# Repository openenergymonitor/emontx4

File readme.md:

# EmonTx v4

The emonTx v4 is an energy monitoring transmitter unit that can monitor up to 6 AC circuits using CT sensors and the OpenEnergyMonitor 1-3 phase voltage sensing unit. At it's core is a Microchip AVR128DB48 microcontroller - responsible for sampling the current and voltage waveforms and calculating the power and energy values. The emonTx v4 also supports temperature sensing and pulse counting.

Data from the emonTx can be transmitted over the 433 MHz RFM69cw radio link or read directly using a USB cable from an emonBase or emonPi. A number of adapter boards are also available to provide internal connectivity options via ESP32, ESP8266, Pi Pico W and Pi Zero W.

**Key features**

* Micro-controller: AVR128DB48 (VQFN 128 kb flash, 48-pin package)
* 3 voltage channels (via RJ11 connector top-right, interfaces with separate voltage sensing board, single phase firmware only at present).
* 6 CT current channels on the base board.
* Option to extend the number of CT channels to 12 via an additional extender board (firmware not yet developed for this).
* Precision voltage reference for the ADC to improve accuracy.
* RJ45 socket for pulse counter and DS18B20 temperature sensing.
* 3x 3-WAY pluggable terminal blocks for selectable temperature sensing, pulse or additional analog input.
* RFM69CW 433MHz radio transceiver
* DIP Switch to select node id
* USB-C power and integrated CP2102 usb to serial chip
* Serial and SPI pin headers breakout internally, designed for use with adapter boards.
 
The dimensions are slightly smaller than that of the emonTx v3 at 65mm long rather than 80mm.

The board is designed to support both single and full 3-phase electricity monitoring when used in conjunction with the relevant external voltage sensing board. And the CT extender pin headers should provide a cost effective way of gaining additional CT channels.

The on-board USB to serial chip will make it easier and neater to have a hard-wired installation linking the emonTx to a RaspberryPi based base station.

## Documentation

[View on read the docs](https://docs.openenergymonitor.org/emontx4/index.html)

Or here on github:

- [Install Guide](docs/emontx4_emonbase_install.md)
- [Configuration](docs/configuration.md)
- [Firmware](docs/firmware.md)
- [Expansion boards](docs/expansion_boards.md)

## Expansion Boards

- [6CT Expansion Board](https://github.com/openenergymonitor/emontx4/tree/main/expansion_boards/CTExt)
- [ESP8266 Expansion Board](https://github.com/openenergymonitor/emontx4/tree/main/expansion_boards/ESP8266)
- [ESP32 Expansion Board](https://github.com/openenergymonitor/emontx4/tree/main/expansion_boards/ESP32)
- [Pi Pico Expansion Board](https://github.com/openenergymonitor/emontx4/tree/main/expansion_boards/PiPico)
- [Pi Zero ExtExpansionension Board](https://github.com/openenergymonitor/emontx4/tree/main/expansion_boards/PiZero)

## Community & Support

- [OpenEnergyMonitor Forums](https://community.openenergymonitor.org)

OpenEnergyMonitor Shop Support: support@openenergymonitor.zendesk.com

## License

- The hardware designs (schematics and CAD files) are licensed under a Creative Commons Attribution-ShareAlike 3.0 Unported License.
- The firmware is released under the GNU GPL V3 license The documentation is subject to GNU Free Documentation License
- The hardware designs follow the terms of the OSHW (Open-source hardware) Statement of Principles 1.0.

## Disclaimer

```
OUR PRODUCTS AND ASSEMBLY KITS MAY BE USED BY EXPERIENCED, SKILLED USERS, AT THEIR OWN RISK. TO THE FULLEST EXTENT PERMISSIBLE BY THE APPLICABLE LAW, WE HEREBY DISCLAIM ANY AND ALL RESPONSIBILITY, RISK, LIABILITY AND DAMAGES ARISING OUT OF DEATH OR PERSONAL INJURY RESULTING FROM ASSEMBLY OR OPERATION OF OUR PRODUCTS.

Your safety is your own responsibility, including proper use of equipment and safety gear, and determining whether you have adequate skill and experience. OpenEnergyMonitor and Megni registered partnership disclaims all responsibility for any resulting damage, injury, or expense. It is your responsibility to make sure that your activities comply with applicable laws, including copyright. Always check the webpage associated with each unit before you get started. There may be important updates or corrections. All use of the instructions, kits, projects and suggestions given both by megni.co.uk, openenergymonitor.org and shop.openenergymonitor.org are to be used at your own risk. The technology (hardware , firmware and software) are constantly changing, documentation (including build guide and instructions) may not be complete or correct.

If you feel uncomfortable with assembling or using any part of the system, return it to us for a full refund.
```

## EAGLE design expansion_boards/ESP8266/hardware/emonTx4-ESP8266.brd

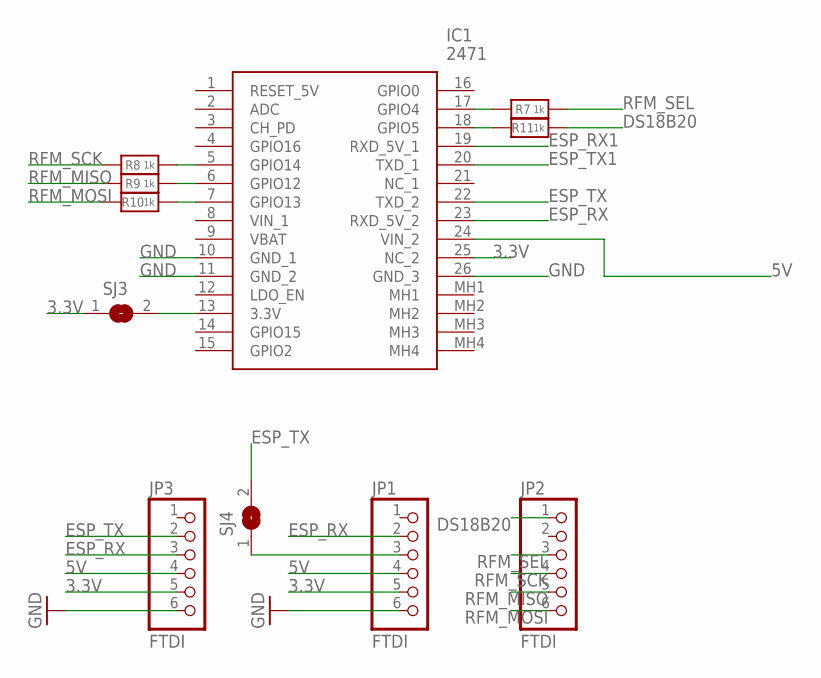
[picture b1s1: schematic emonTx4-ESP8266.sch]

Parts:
IC1: 2471
JP1, JP2, JP3: FTDI; 1X06_ROUND_70
R7, R8, R9, R10, R11: 1k; _0603
SJ3, SJ4: SJ

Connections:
3.3V: IC1.25 (NC_2), JP1.5, JP3.5, SJ3.1
5V: IC1.24 (VIN_2), JP1.4, JP3.4
DS18B20: JP2.1, R11.1
ESP_RX: IC1.23 (RXD_5V_2), JP1.2, JP3.3
ESP_RX1: IC1.19 (RXD_5V_1)
ESP_TX: IC1.22 (TXD_2), JP3.2, SJ4.2
ESP_TX1: IC1.20 (TXD_1)
GND: IC1.10 (GND_1), IC1.11 (GND_2), IC1.26 (GND_3), JP1.6, JP3.6
unnamed: JP1.3, SJ4.1
unnamed: IC1.13 (3.3V), SJ3.2
unnamed: IC1.17 (GPIO4), R7.2
unnamed: IC1.5 (GPIO14), R8.1
unnamed: IC1.6 (GPIO12), R9.1
unnamed: IC1.7 (GPIO13), R10.1
unnamed: IC1.18 (GPIO5), R11.2
RFM_MISO: JP2.5, R9.2
RFM_MOSI: JP2.6, R10.2
RFM_SCK: JP2.4, R8.2
RFM_SEL: JP2.3, R7.1

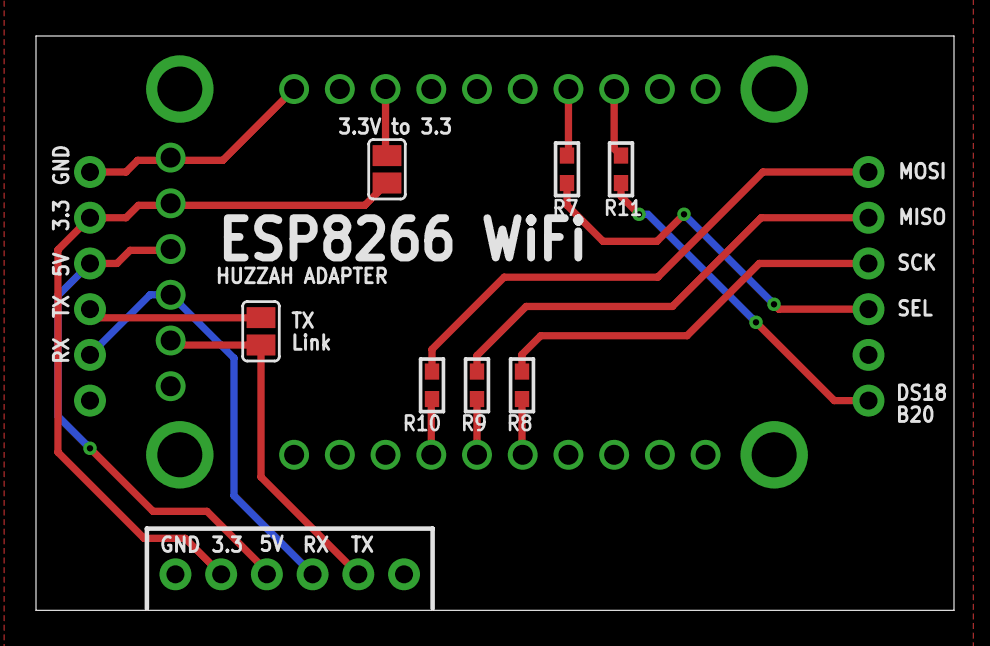
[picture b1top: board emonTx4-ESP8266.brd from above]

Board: 2 copper layers, 51.0 x 31.9 mm, 11 parts (1 on the bottom side), 17 nets.

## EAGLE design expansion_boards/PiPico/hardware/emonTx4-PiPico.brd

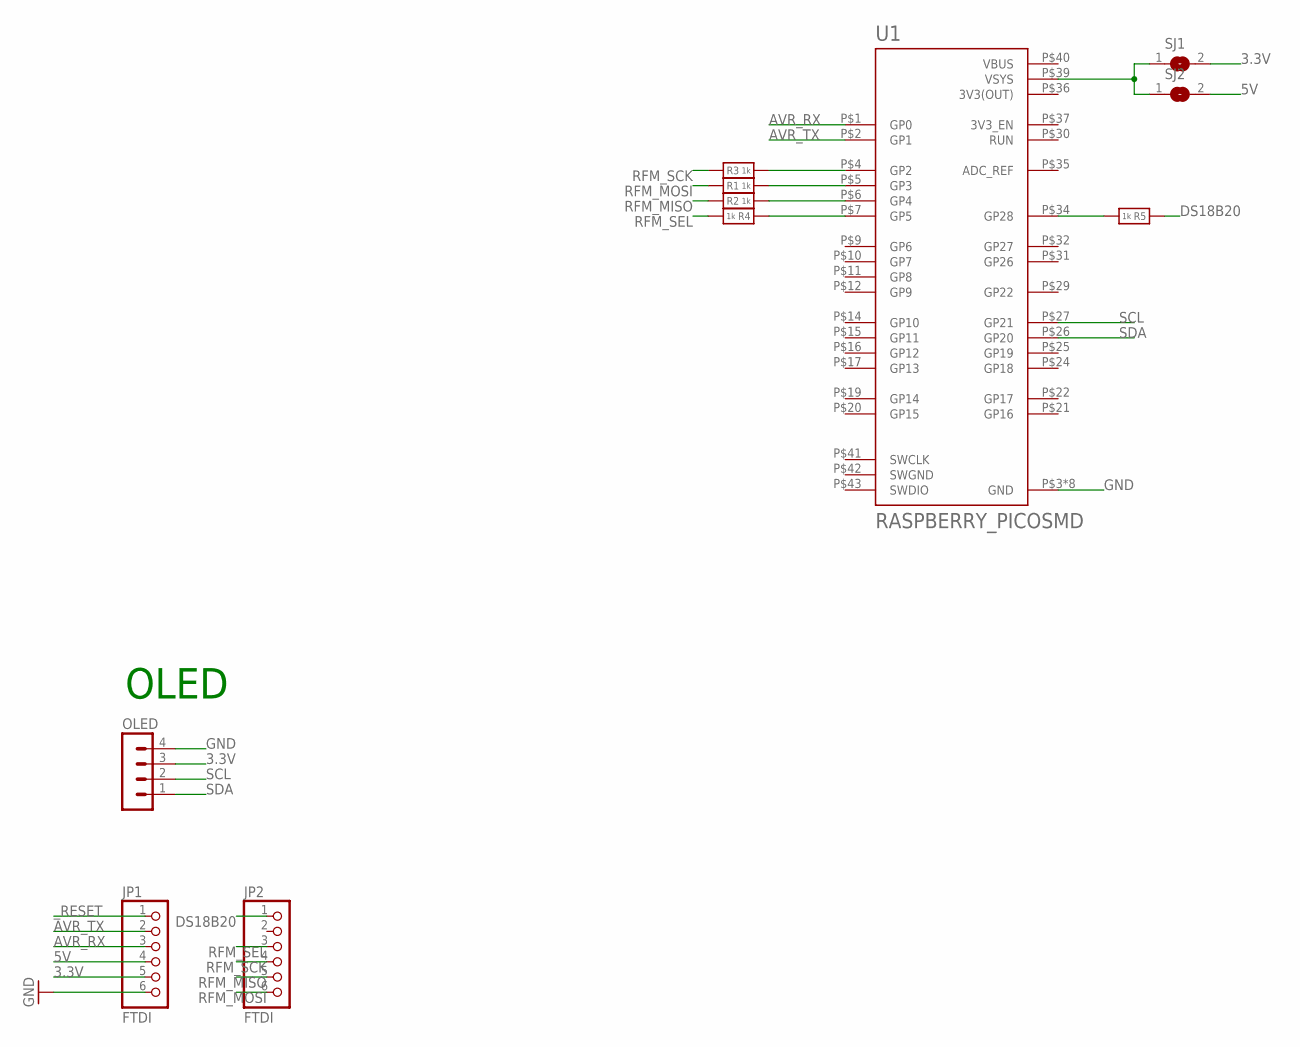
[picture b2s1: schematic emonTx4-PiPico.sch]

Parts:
JP1, JP2: FTDI; 1X06_ROUND_70
OLED: MA04-1-OLEDOLED; MA04-1-OLED
R1, R2, R3, R4, R5: 1k; _0603
SJ1, SJ2: SJ
U1: RASPBERRY_PICOSMD; PICO-PKG-SMD

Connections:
3.3V: JP1.5, OLED.3, SJ1.2
3V3(OUT): U1.P$36 (3V3(OUT))
5V: JP1.4, SJ2.2
AVR_RX: JP1.3, U1.P$1 (GP0)
AVR_TX: JP1.2, U1.P$2 (GP1)
DS18B20: JP2.1, R5.2
GND: JP1.6, OLED.4, U1.P$3 (GND), U1.P$8 (GND), U1.P$13 (GND), U1.P$18 (GND), U1.P$23 (GND), U1.P$28 (GND), U1.P$33 (GND), U1.P$38 (GND)
unnamed: SJ1.1, SJ2.1, U1.P$39 (VSYS)
unnamed: R3.1, U1.P$4 (GP2)
unnamed: R1.1, U1.P$5 (GP3)
unnamed: R2.1, U1.P$6 (GP4)
unnamed: R4.2, U1.P$7 (GP5)
unnamed: R5.1, U1.P$34 (GP28)
RFM_MISO: JP2.5, R2.2
RFM_MOSI: JP2.6, R1.2
RFM_SCK: JP2.4, R3.2
RFM_SEL: JP2.3, R4.1
SCL: OLED.2, U1.P$27 (GP21)
SDA: OLED.1, U1.P$26 (GP20)
SWGND: U1.P$42 (SWGND)
VBUS: U1.P$40 (VBUS)
_RESET: JP1.1

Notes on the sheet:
OLED

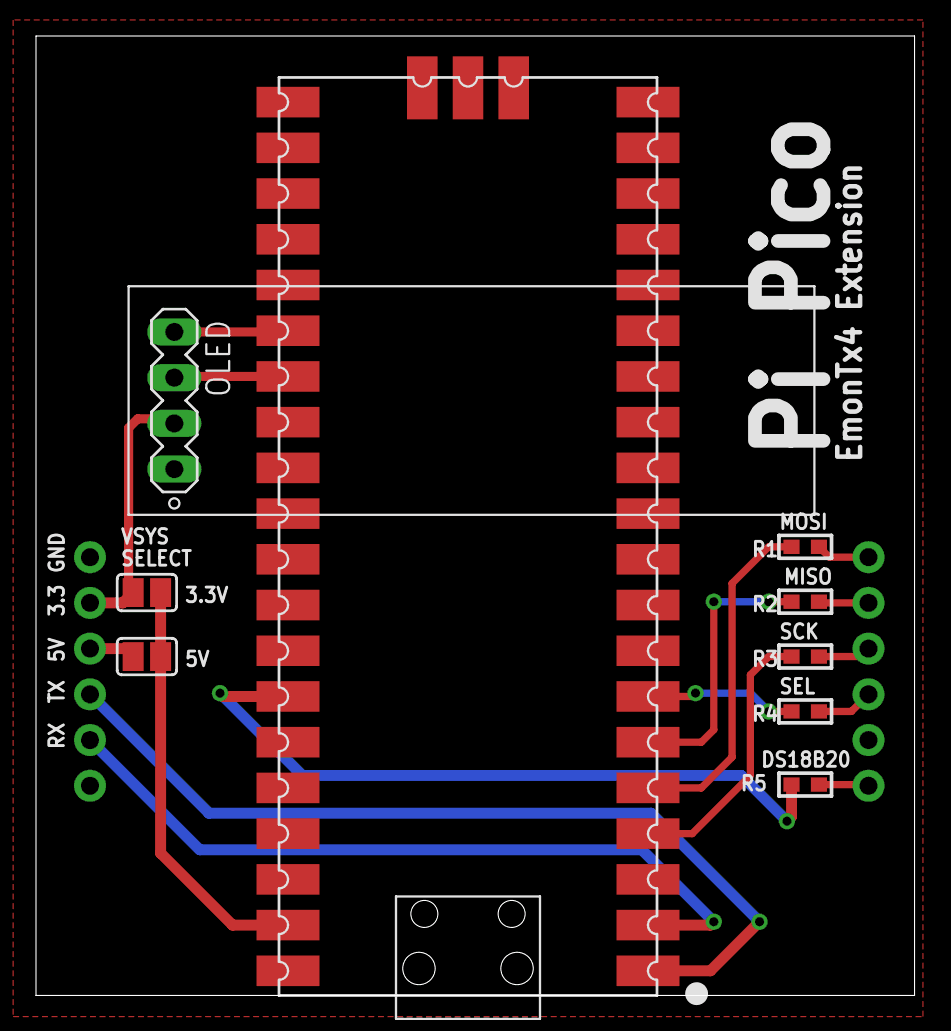
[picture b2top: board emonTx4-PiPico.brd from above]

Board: 2 copper layers, 48.8 x 53.3 mm, 11 parts (0 on the bottom side), 18 nets.

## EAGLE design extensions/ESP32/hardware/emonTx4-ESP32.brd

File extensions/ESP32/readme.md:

# EmonTx v4 ESP32 Extension Board

### Software examples:

- [Basic emoncms client](https://github.com/openenergymonitor/emontx4/tree/main/extensions/ESP32/examples/basic_emoncms_client)
- [RFM69cw test](https://github.com/openenergymonitor/emontx4/tree/main/extensions/ESP32/examples/rfm69cw_test)

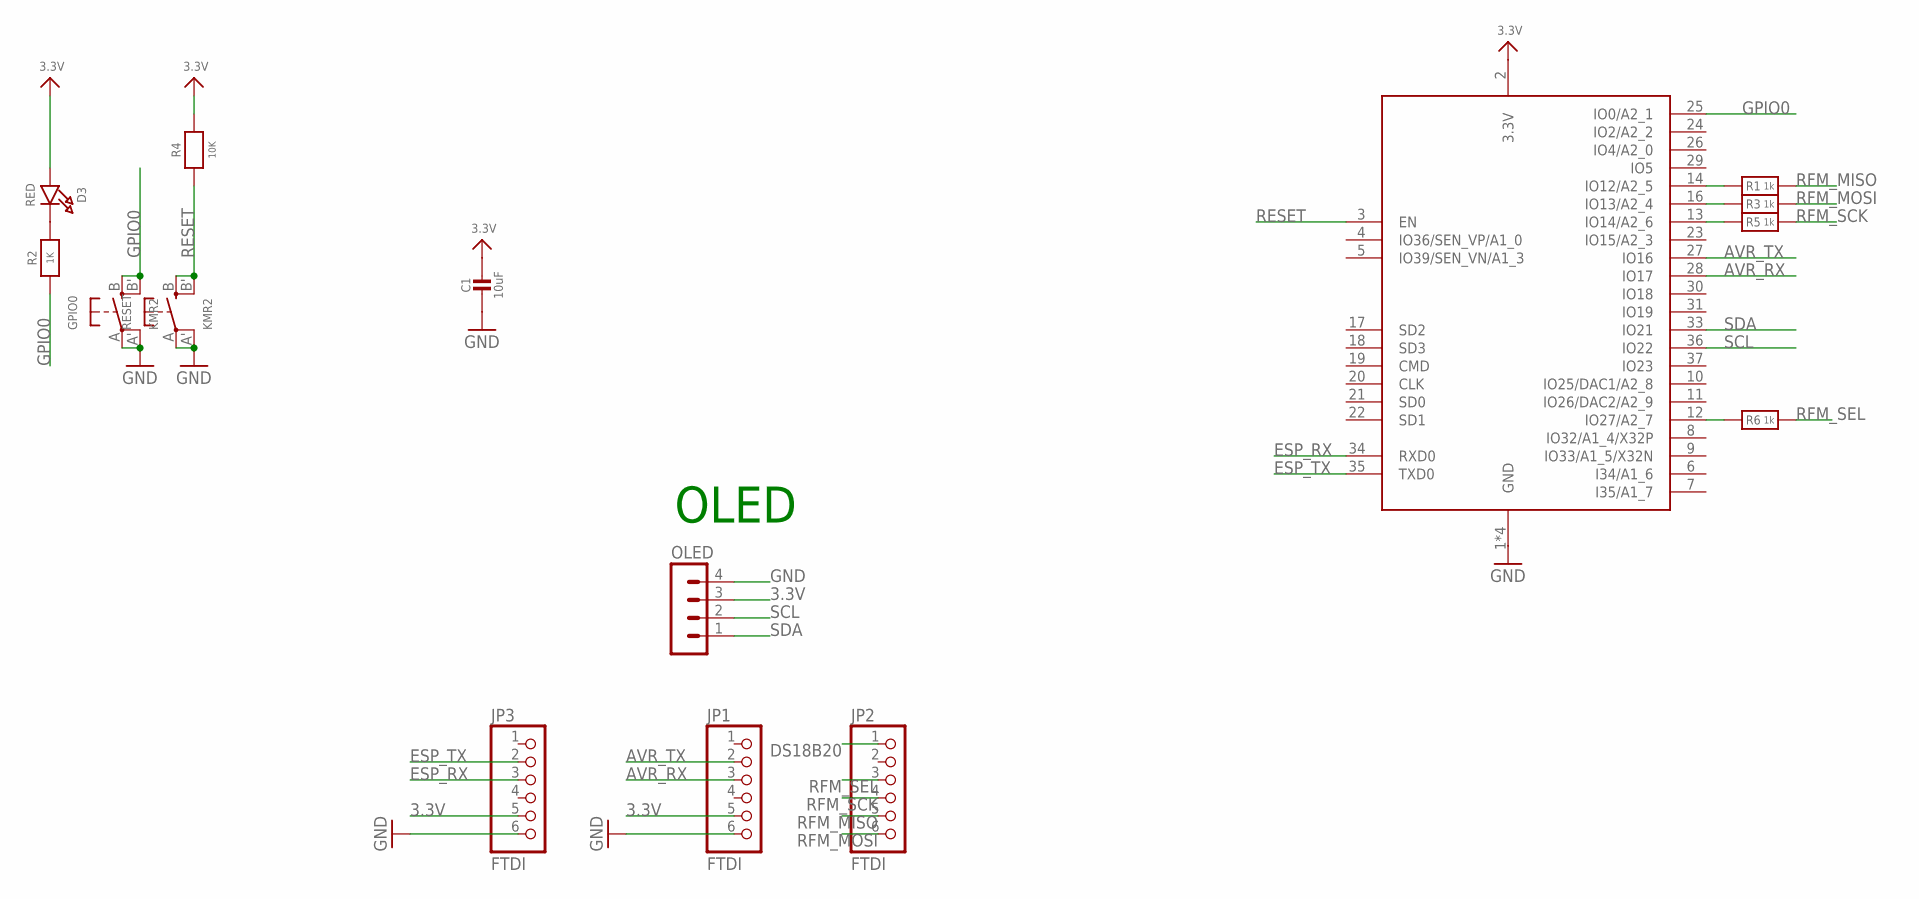
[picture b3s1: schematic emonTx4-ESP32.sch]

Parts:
C1: 10uF; _0603
D3: RED; CHIPLED_0603
GPIO0: KMR2; BTN_KMR2_4.6X2.8
JP1, JP2, JP3: FTDI; 1X06_ROUND_70
OLED: MA04-1-OLEDOLED; MA04-1-OLED
R1, R3, R5, R6: 1k; _0603
R2: 1K; _0603
R4: 10K; _0603
RESET: KMR2; BTN_KMR2_4.6X2.8
X2: ESP32_WROOM32; WROOM32

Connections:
3.3V: C1.1, D3.A, JP1.5, JP3.5, OLED.3, R4.2, X2.2 (3.3V)
AVR_RX: JP1.3, X2.28 (IO17)
AVR_TX: JP1.2, X2.27 (IO16)
DS18B20: JP2.1
ESP_RX: JP3.3, X2.34 (RXD0)
ESP_TX: JP3.2, X2.35 (TXD0)
GND: C1.2, GPIO0.A, GPIO0.A' (P1), JP1.6, JP3.6, OLED.4, RESET.A, RESET.A' (P1), X2.1 (GND), X2.15 (GND), X2.38 (GND), X2.P$1 (GND)
GPIO0: GPIO0.B (S), GPIO0.B' (S1), R2.1, X2.25 (IO0/A2_1)
unnamed: D3.C, R2.2
unnamed: R1.2, X2.14 (IO12/A2_5)
unnamed: R3.2, X2.16 (IO13/A2_4)
unnamed: R5.2, X2.13 (IO14/A2_6)
unnamed: R6.2, X2.12 (IO27/A2_7)
RESET: R4.1, RESET.B (S), RESET.B' (S1), X2.3 (EN)
RFM_MISO: JP2.5, R1.1
RFM_MOSI: JP2.6, R3.1
RFM_SCK: JP2.4, R5.1
RFM_SEL: JP2.3, R6.1
SCL: OLED.2, X2.36 (IO22)
SDA: OLED.1, X2.33 (IO21)

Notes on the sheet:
OLED

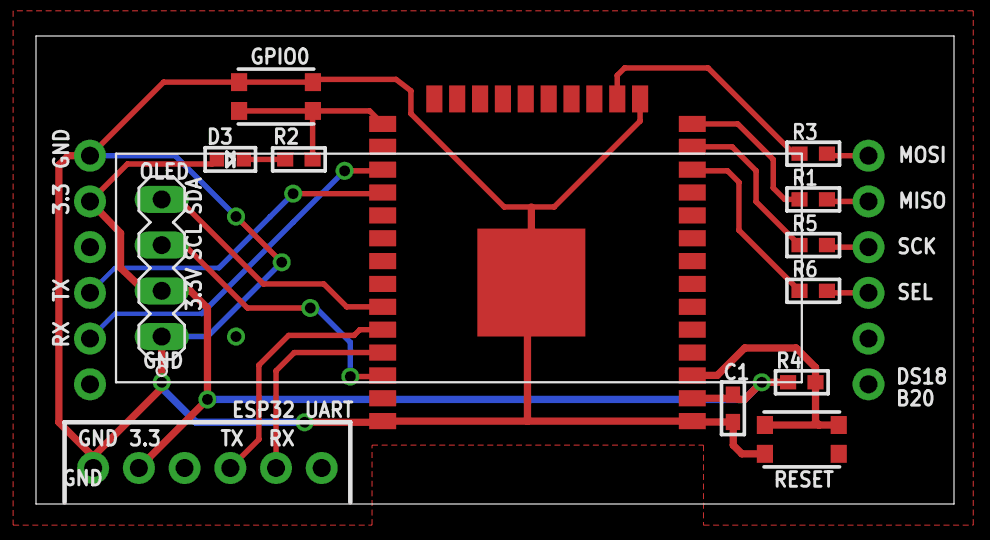
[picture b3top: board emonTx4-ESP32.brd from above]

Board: 2 copper layers, 51.0 x 26.0 mm, 15 parts (0 on the bottom side), 19 nets.

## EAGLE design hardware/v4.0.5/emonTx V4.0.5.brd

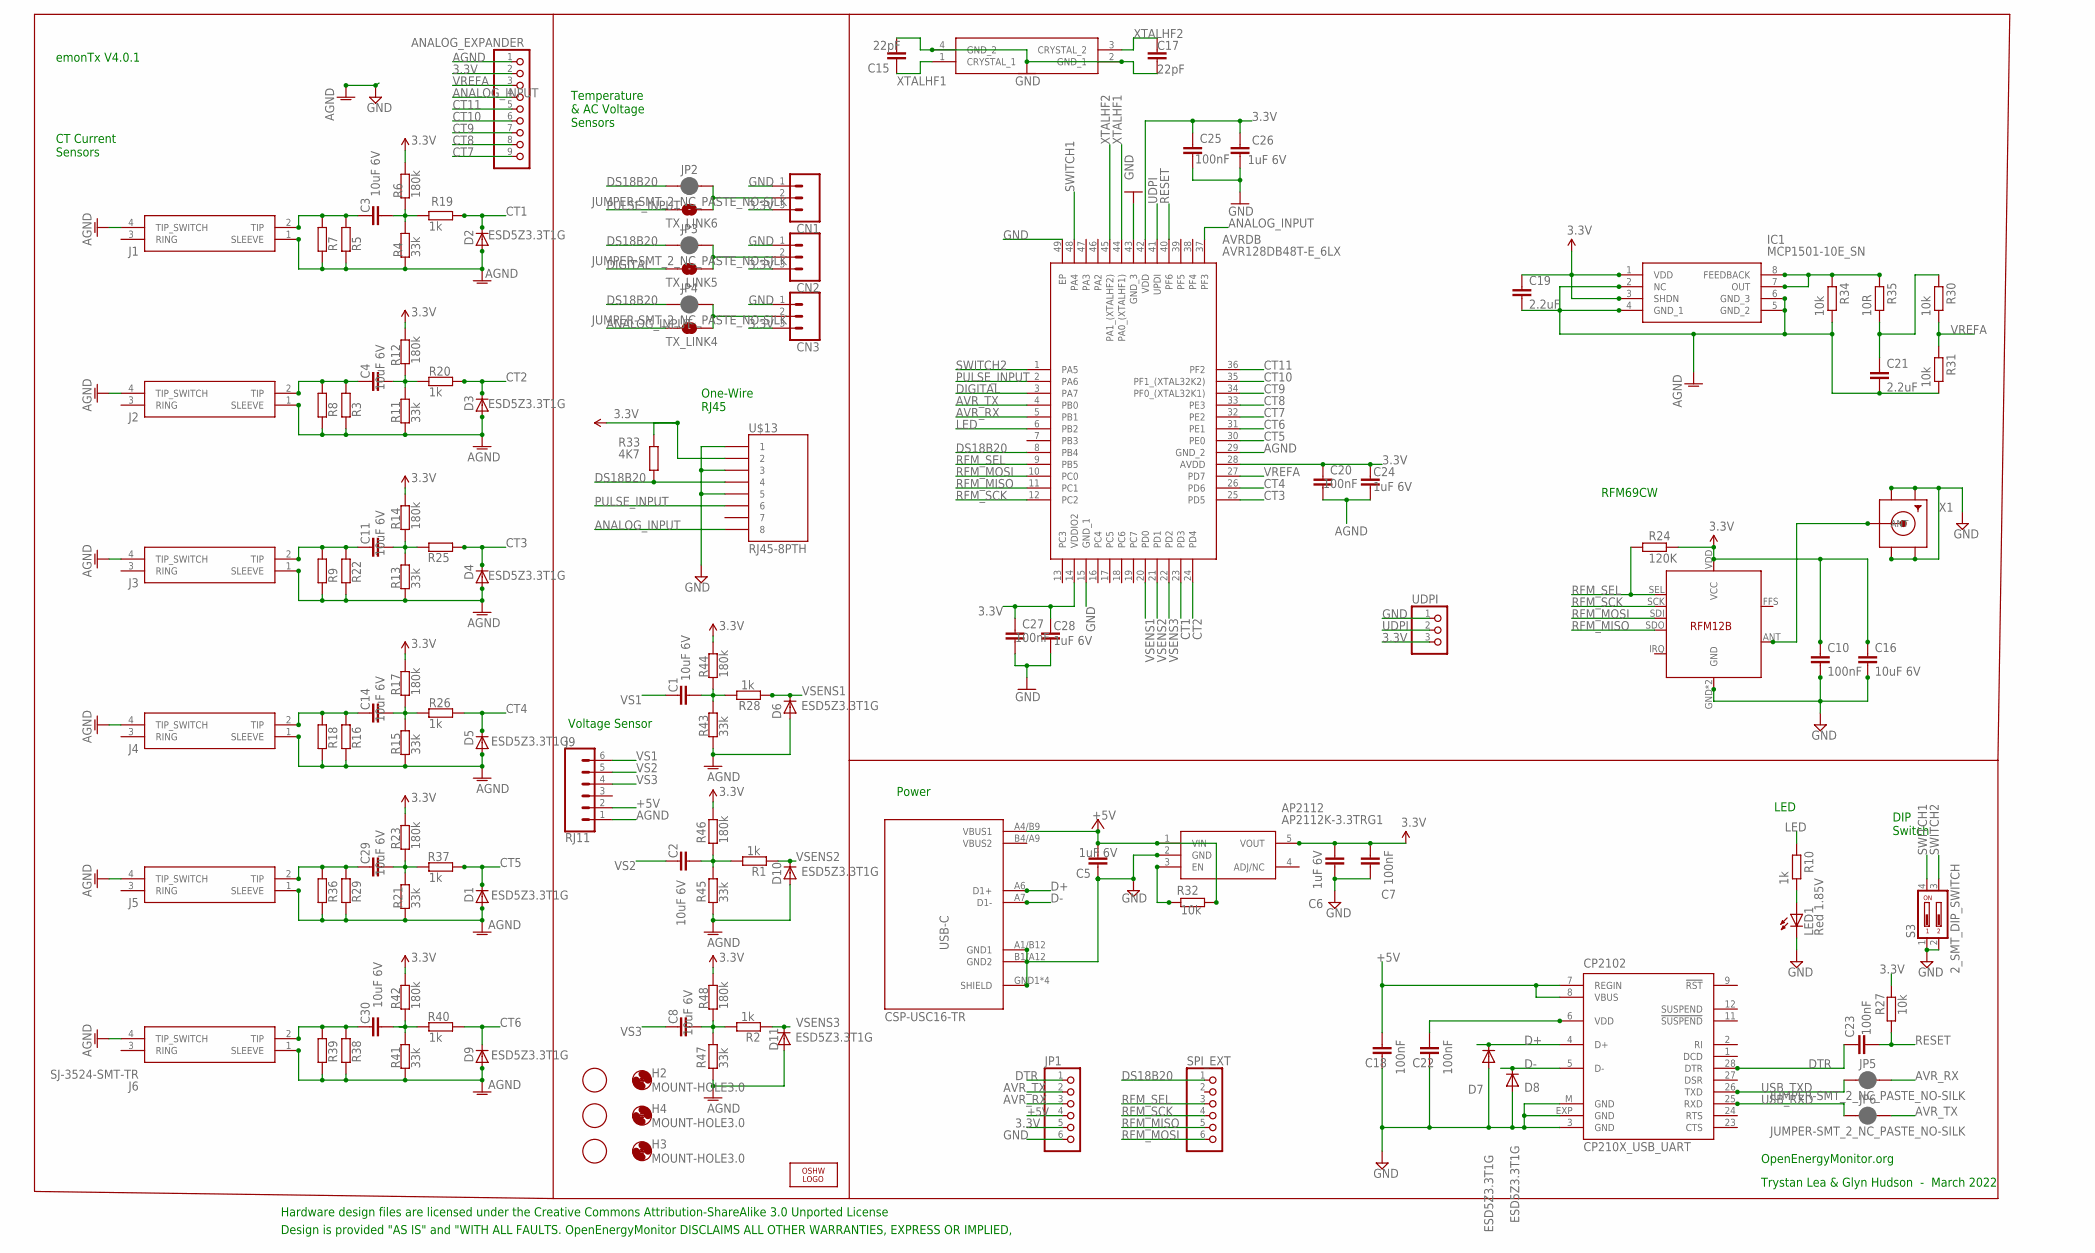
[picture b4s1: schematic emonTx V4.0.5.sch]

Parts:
ANALOG_EXPANDER: PINHD-1X9; 1X09-BIG
AP2112: AP2112K-3.3TRG1; SOT95P282X130-5N
AVRDB: AVR128DB48T-E_6LX; QFN40P600X600X90-49N
C1, C2, C3, C4, C8, C11, C14, C16, C29, C30: 10uF 6V; C0603
C5, C6, C24, C26, C28: 1uF 6V; C0603
C7, C10, C18, C20, C22, C23, C25, C27: 100nF; C0603
C15, C17: 22pF; C0603
C19, C21: 2.2uF; C0603
CN1, CN2, CN3: CONN_03SCREW; SCREWTERMINAL-3.5MM-3
CP2102: CP210X_USB_UART; MLP28
D1, D2, D3, D4, D5, D6, D7, D8, D9, D10, D11: ESD5Z3.3T1G; SOD-523
H2, H3, H4: MOUNT-HOLE3.0; 3,0
IC1: MCP1501-10E_SN; SOIC127P600X175-8N
J1, J2, J3, J4, J5, J6: SJ-3524-SMT-TR
J9: RJ11; RJ11-6
JP1: PINHD-1X6; 1X06
JP2, JP3, JP4, JP5, JP6: JUMPER-SMT_2_NC_PASTE_NO-SILK; SMT-JUMPER_2_NC_PASTE_NO-SILK
LED1: Red 1.85V; CHIP-LED0805
LOGO1: OSHW_LOGO_6MILX0200-NT; OSHW_6X200_NOTEXT
R1, R2, R10, R19, R20, R25, R26, R28, R37, R40: 1k; R0603
R3, R5, R16, R22, R29, R38: R-EU_0204/7; 0204/7
R4, R11, R13, R15, R21, R41, R43, R45, R47: 33k; R0603
R6, R12, R14, R17, R23, R42, R44, R46, R48: 180k; R0603
R7, R8, R9, R18, R36, R39: R-EU_R1206; R1206
R24: 120K; R0603
R27, R30, R31, R32, R34: 10k; R0603
R33: 4K7; R0603
R35: 10R; R0603
S3: 2_SMT_DIP_SWITCH; DIP_SWITCH_SMT
SPI_EXT: PINHD-1X6; 1X06
TX_LINK4, TX_LINK5, TX_LINK6: SOLDERJUMPERNC; SJ_2S
U$4, U$5, U$7: FIDUCIAL; FIDUCIAL_1MM
U$13: RJ45-8PTH; RJ45-8
U$14: RFM12B
UDPI: PINHD-1X3; 1X03
USB-C: CSP-USC16-TR; USB-C
X1: SMACONNECTOR; SMA90_DIP
XTAL: MCSJK-7U-12.00-12-10-80-B-10; MCSJK7U1200121080B10

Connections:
3.3V: ANALOG_EXPANDER.2, AP2112.5 (VOUT), AVRDB.14 (VDDIO2), AVRDB.28 (AVDD), AVRDB.42 (VDD), C6.2, C7.2, C10.1, C16.1, C19.1, C20.1, C24.1, C25.1, C26.1, C27.1, C28.1, CN1.3, CN2.3, CN3.3, IC1.1 (VDD), IC1.3 (SHDN), JP1.5, R6.2, R12.2, R14.2, R17.2, R23.2, R24.2, R27.2, R33.1, R42.2, R44.2, R46.2, R48.2, U$13.2, U$14.VDD (VCC), UDPI.3
+5V: AP2112.1 (VIN), C5.2, C18.2, CP2102.7 (REGIN), CP2102.8 (VBUS), J9.2, JP1.4, R32.1, USB-C.A4/B9 (VBUS1)
AGND: ANALOG_EXPANDER.1, AVRDB.29 (GND_2), C19.2, C20.2, C21.2, C24.2, D1.A, D2.A, D3.A, D4.A, D5.A, D6.A, D9.A, D10.A, D11.A, IC1.2 (NC), IC1.4 (GND_1), IC1.5 (GND_2), IC1.6 (GND_3), J1.1 (SLEEVE), J1.4 (TIP_SWITCH), J2.1 (SLEEVE), J2.4 (TIP_SWITCH), J3.1 (SLEEVE), J3.4 (TIP_SWITCH), J4.1 (SLEEVE), J4.4 (TIP_SWITCH), J5.1 (SLEEVE), J5.4 (TIP_SWITCH), J6.1 (SLEEVE), J6.4 (TIP_SWITCH), J9.1, R3.1, R4.2, R5.1, R7.1, R8.1, R9.1, R11.2, R13.2, R15.2, R16.1, R18.1, R21.2, R22.1, R29.1, R31.1, R34.1, R36.1, R38.1, R39.1, R41.2, R43.2, R45.2, R47.2
ANALOG_INPUT: ANALOG_EXPANDER.4, AVRDB.37 (PF3), TX_LINK4.1, U$13.8
AVR_RX: AVRDB.5 (PB1), JP1.3, JP5.2
AVR_TX: AVRDB.4 (PB0), JP1.2, JP6.2
CT1: AVRDB.23 (PD3), D2.K (C), R19.2
CT2: AVRDB.24 (PD4), D3.K (C), R20.2
CT3: AVRDB.25 (PD5), D4.K (C), R25.1
CT4: AVRDB.26 (PD6), D5.K (C), R26.2
CT5: AVRDB.30 (PE0), D1.K (C), R37.2
CT6: AVRDB.31 (PE1), D9.K (C), R40.2
CT7: ANALOG_EXPANDER.9, AVRDB.32 (PE2)
CT8: ANALOG_EXPANDER.8, AVRDB.33 (PE3)
CT9: ANALOG_EXPANDER.7, AVRDB.34 (PF0_(XTAL32K1))
CT10: ANALOG_EXPANDER.6, AVRDB.35 (PF1_(XTAL32K2))
CT11: ANALOG_EXPANDER.5, AVRDB.36 (PF2)
D+: CP2102.4 (D+), D7.K (C), USB-C.A6 (D1+)
D-: CP2102.5 (D-), D8.K (C), USB-C.A7 (D1-)
DIG1: U$14.ANT, X1.ANTENNA (ANT)
DIGITAL: AVRDB.3 (PA7), TX_LINK5.1
DS18B20: AVRDB.8 (PB4), JP2.1, JP3.1, JP4.1, R33.2, SPI_EXT.1, U$13.4
DTR: C23.1, CP2102.28 (DTR), JP1.1
GND: AP2112.2 (GND), AVRDB.15 (GND_1), AVRDB.43 (GND_3), AVRDB.49 (EP), C5.1, C6.1, C7.1, C10.2, C15.2, C16.2, C17.2, C18.1, C22.1, C25.2, C26.2, C27.2, C28.2, CN1.1, CN2.1, CN3.1, CP2102.3 (GND), CP2102.EXP (GND), CP2102.M (GND), D7.A, D8.A, JP1.6, LED1.C, S3.1, S3.2, U$13.1, U$13.3, U$13.5, U$14.GND, U$14.P$12 (GND), UDPI.1, USB-C.A1/B12 (GND1), USB-C.B1/A12 (GND2), USB-C.GND1 (SHIELD), USB-C.GND2 (SHIELD), USB-C.GND3 (SHIELD), USB-C.GND4 (SHIELD), X1.GND1, X1.GND2, X1.GND3, X1.GND4, XTAL.2 (GND_1), XTAL.4 (GND_2)
LED: AVRDB.6 (PB2), R10.2
unnamed: AP2112.3 (EN), R32.2
unnamed: C30.1, J6.2 (TIP), R38.2, R39.2
unnamed: C11.1, J3.2 (TIP), R9.2, R22.2
unnamed: C22.2, CP2102.6 (VDD)
unnamed: C30.2, R40.1, R41.1, R42.1
unnamed: C21.1, R30.2, R35.1
unnamed: C3.2, R4.1, R6.1, R19.1
unnamed: C14.1, J4.2 (TIP), R16.2, R18.2
unnamed: C14.2, R15.1, R17.1, R26.1
unnamed: C3.1, J1.2 (TIP), R5.2, R7.2
unnamed: C4.2, R11.1, R12.1, R20.1
unnamed: C29.1, J5.2 (TIP), R29.2, R36.2
unnamed: C4.1, J2.2 (TIP), R3.2, R8.2
unnamed: C1.2, R28.2, R43.1, R44.1
unnamed: CN1.2, JP2.2, TX_LINK6.2
unnamed: CN2.2, JP3.2, TX_LINK5.2
unnamed: C2.2, R1.2, R45.1, R46.1
unnamed: CN3.2, JP4.2, TX_LINK4.2
unnamed: C8.2, R2.2, R47.1, R48.1
unnamed: IC1.7 (OUT), IC1.8 (FEEDBACK), R34.2, R35.2
unnamed: C29.2, R21.1, R23.1, R37.1
unnamed: C11.2, R13.1, R14.1, R25.2
unnamed: LED1.A, R10.1
PULSE_INPUT: AVRDB.2 (PA6), TX_LINK6.1, U$13.6
RESET: AVRDB.40 (PF6), C23.2, R27.1
RFM_MISO: AVRDB.11 (PC1), SPI_EXT.5, U$14.SDO
RFM_MOSI: AVRDB.10 (PC0), SPI_EXT.6, U$14.SDI
RFM_SCK: AVRDB.12 (PC2), SPI_EXT.4, U$14.SCK
RFM_SEL: AVRDB.9 (PB5), R24.1, SPI_EXT.3, U$14.SEL
SWITCH1: AVRDB.48 (PA4), S3.4
SWITCH2: AVRDB.1 (PA5), S3.3
UDPI: AVRDB.41 (UPDI), UDPI.2
USB_RXD: CP2102.25 (RXD), JP6.1
USB_TXD: CP2102.26 (TXD), JP5.1
VREFA: ANALOG_EXPANDER.3, AVRDB.27 (PD7), R30.1, R31.2
VS1: C1.1, J9.6
VS2: C2.1, J9.5
VS3: C8.1, J9.4
VSENS1: AVRDB.20 (PD0), D6.K (C), R28.1
VSENS2: AVRDB.21 (PD1), D10.K (C), R1.1
VSENS3: AVRDB.22 (PD2), D11.K (C), R2.1
XTALHF1: AVRDB.44 (PA0_(XTALHF1)), C15.1, XTAL.1 (CRYSTAL_1)
XTALHF2: AVRDB.45 (PA1_(XTALHF2)), C17.1, XTAL.3 (CRYSTAL_2)

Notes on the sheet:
Voltage Sensor
OpenEnergyMonitor.org
Trystan Lea & Glyn Hudson - March 2022
Power
CT Current Sensors
Temperature & AC Voltage Sensors
Design is provided "AS IS" and "WITH ALL FAULTS. OpenEnergyMonitor DISCLAIMS ALL OTHER WARRANTIES, EXPRESS OR IMPLIED,
Hardware design files are licensed under the Creative Commons Attribution-ShareAlike 3.0 Unported License
emonTx V4.0.1
RFM69CW
One-Wire RJ45
DIP Switch
LED

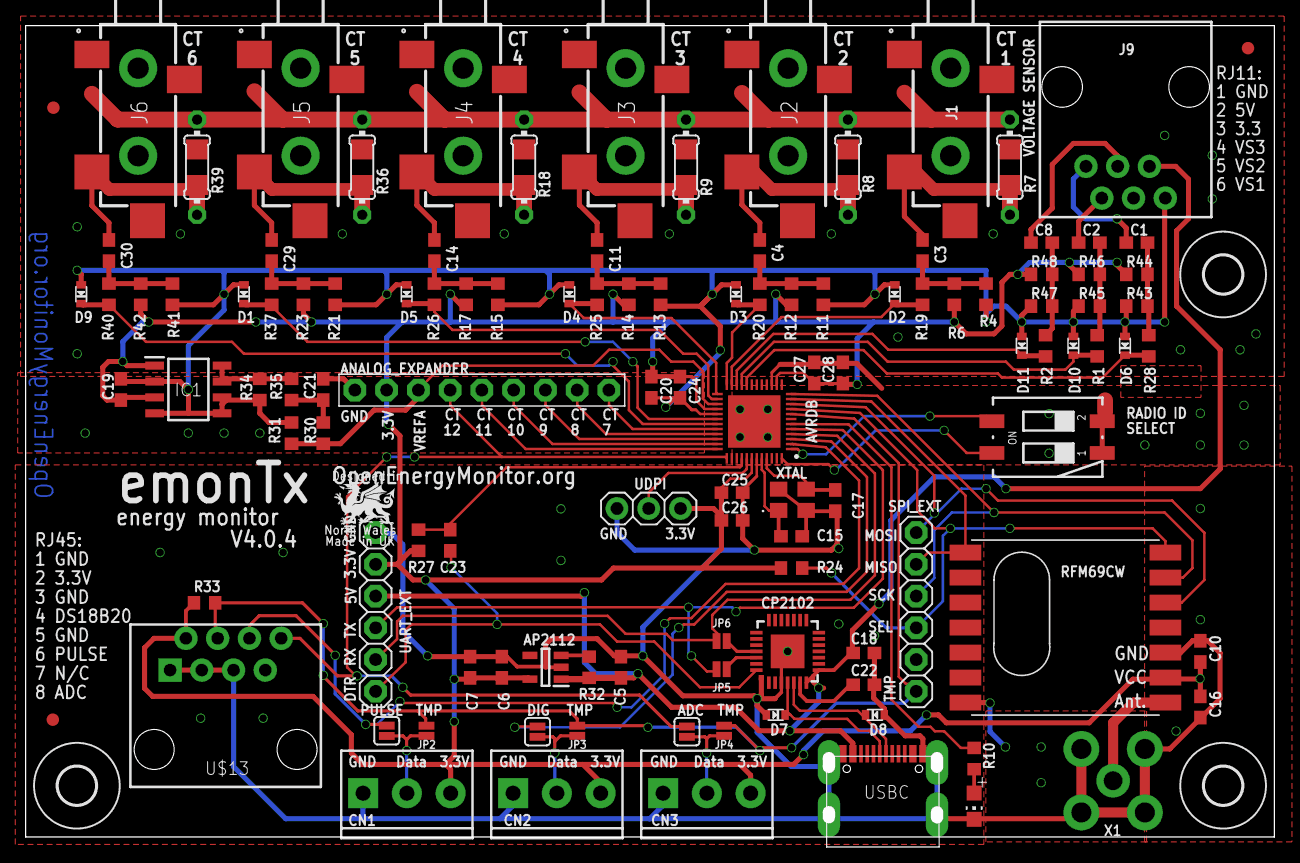
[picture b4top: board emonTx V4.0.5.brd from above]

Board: 2 copper layers, 99.9 x 64.9 mm, 126 parts (1 on the bottom side), 68 nets.

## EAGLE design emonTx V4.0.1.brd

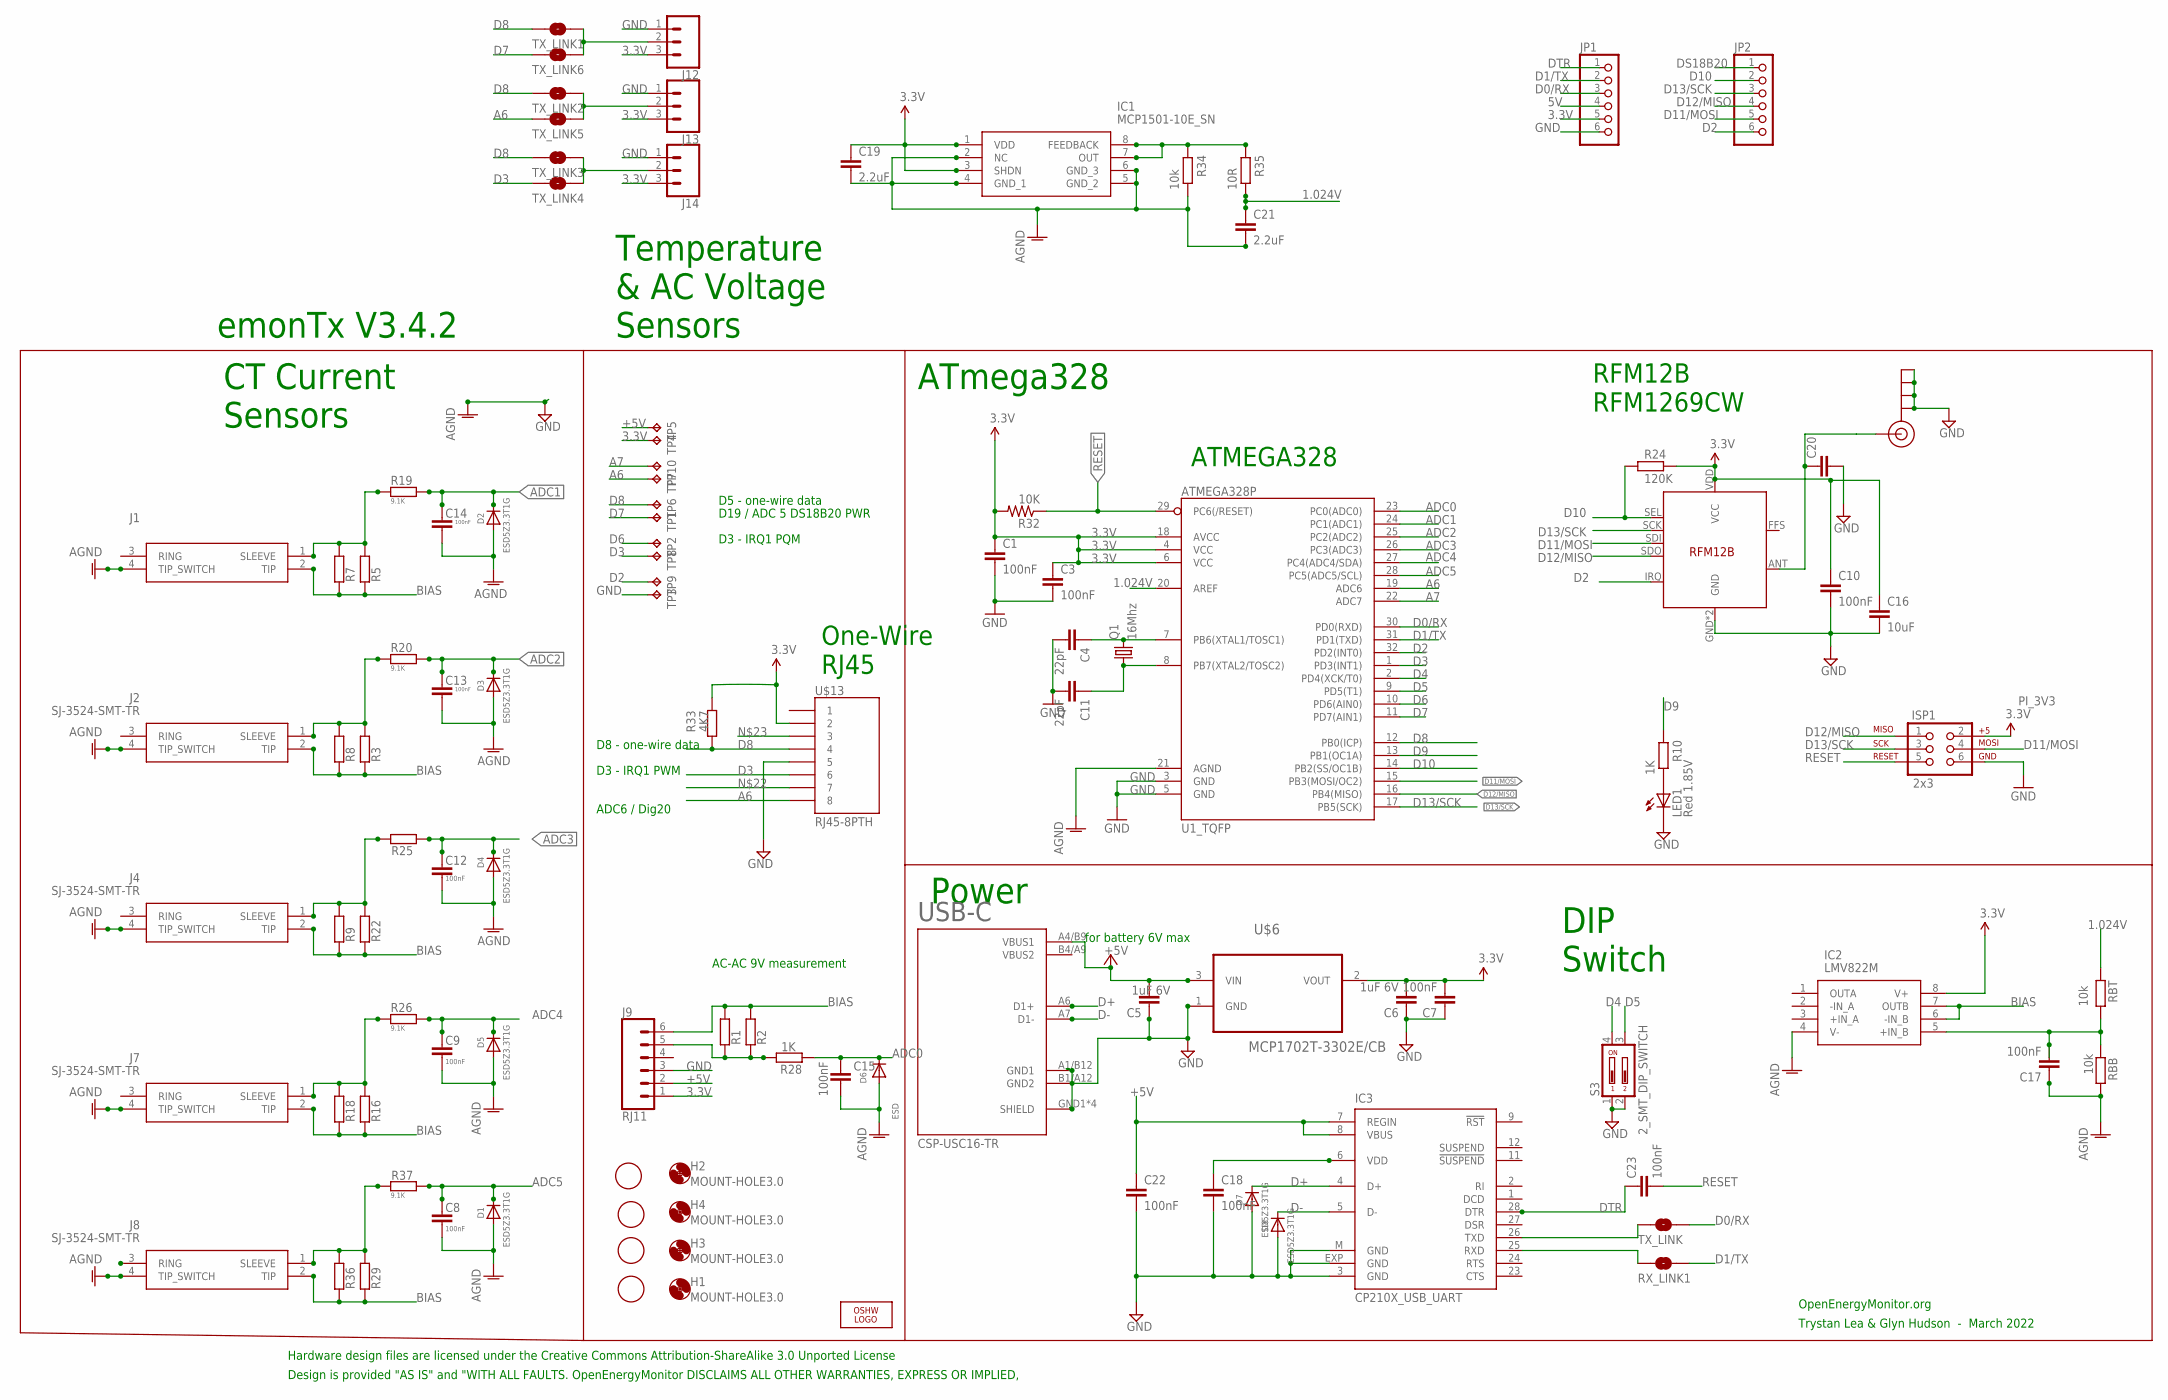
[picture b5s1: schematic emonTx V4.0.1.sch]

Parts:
C1, C3, C7, C8, C9, C10, C12, C13, C14, C15, C17, C23: 100nF; C0603
C4, C11: 22pF; C0603
C5, C6: 1uF 6V; C0603
C16: 10uF; C0603
C18, C22: 100nF; 0603-CAP
C19, C21: 2.2uF; C0603
C20: ant tune?; C0603
D1, D2, D3, D4, D5, D7, D8: ESD5Z3.3T1G; SOD-523
D6: ESD; SOD-523
H1, H2, H3, H4: MOUNT-HOLE3.0; 3,0
IC1: MCP1501-10E_SN; SOIC127P600X175-8N
IC2: LMV822M; SOIC127P600X175-8N
IC3: CP210X_USB_UART; MLP28
ISP1: 2x3; 2X3
J1, J2, J4, J7, J8: SJ-3524-SMT-TR
J9: RJ11; RJ11-6
J12, J13, J14: CONN_03SCREW; SCREWTERMINAL-3.5MM-3
J$1: SMA_EDGE; SMA-EDGE
JP1, JP2: PINHD-1X6; 1X06
LED1: Red 1.85V; CHIP-LED0805
LOGO1: OSHW_LOGO_6MILX0200-NT; OSHW_6X200_NOTEXT
Q1: 16Mhz; HC49UP
R1, R3, R5, R16, R22, R29: R-EU_0204/7; 0204/7
R2, R7, R8, R9, R18, R36: R-EU_R1206; R1206
R10, R28: 1K; R0603
R19, R20, R25, R26, R37: 9.1K; R0603
R24: 120K; R0603
R32: 10K; R0603
R33: 4K7; R0603
R34: 10k; R0603
R35: 10R; R0603
RBB: 10k; R0603
RBT: 10k; R0603
RX_LINK1: SOLDERJUMPERNC; SJ_2S
S3: 2_SMT_DIP_SWITCH; DIP_SWITCH_SMT
TP1, TP2, TP3, TP4, TP5, TP6, TP7, TP8, TP9, TP10: TPPAD1-13; P1-13
TX_LINK, TX_LINK1, TX_LINK2, TX_LINK3, TX_LINK4, TX_LINK5, TX_LINK6: SOLDERJUMPERNC; SJ_2S
U1_TQFP: ATMEGA328P; TQFP32-08
U$1, U$4, U$5, U$7: FIDUCIAL; FIDUCIAL_1MM
U$6: MCP1702T-3302E/CB; SOT95P237X112-3N
U$13: RJ45-8PTH; RJ45-8
U$14: RFM12B
USB-C: CSP-USC16-TR; USB-C

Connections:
1.024V: C21.1, R35.1, RBT.2, U1_TQFP.20 (AREF)
3.3V: C1.1, C3.1, C6.2, C7.2, C10.1, C16.1, C19.1, IC1.1 (VDD), IC1.3 (SHDN), IC2.8 (V+), ISP1.2, J9.1, J12.3, J13.3, J14.3, JP1.5, R24.2, R32.2, R33.1, TP4.TP, U1_TQFP.4 (VCC), U1_TQFP.6 (VCC), U1_TQFP.18 (AVCC), U$6.2 (VOUT), U$13.2, U$14.VDD (VCC)
5V: JP1.4
+5V: C5.2, C22.1, IC3.7 (REGIN), IC3.8 (VBUS), J9.2, TP5.TP, U$6.3 (VIN), USB-C.A4/B9 (VBUS1)
A6: TP7.TP, TX_LINK5.1, U1_TQFP.19 (ADC6), U$13.8
A7: TP10.TP, U1_TQFP.22 (ADC7)
ADC0: C15.1, D6.K (C), R28.1, U1_TQFP.23 (PC0(ADC0))
ADC1: C14.1, D2.K (C), R19.2, U1_TQFP.24 (PC1(ADC1))
ADC2: C13.1, D3.K (C), R20.2, U1_TQFP.25 (PC2(ADC2))
ADC3: C12.1, D4.K (C), R25.1, U1_TQFP.26 (PC3(ADC3))
ADC4: C9.1, D5.K (C), R26.2, U1_TQFP.27 (PC4(ADC4/SDA))
ADC5: C8.1, D1.K (C), R37.2, U1_TQFP.28 (PC5(ADC5/SCL))
AGND: C8.2, C9.2, C12.2, C13.2, C14.2, C15.2, C17.1, C19.2, C21.2, D1.A, D2.A, D3.A, D4.A, D5.A, D6.A, IC1.2 (NC), IC1.4 (GND_1), IC1.5 (GND_2), IC1.6 (GND_3), IC2.4 (V-), J1.4 (TIP_SWITCH), J2.4 (TIP_SWITCH), J4.4 (TIP_SWITCH), J7.4 (TIP_SWITCH), J8.4 (TIP_SWITCH), R34.1, RBB.1, U1_TQFP.21 (AGND)
BIAS: IC2.6 (-IN_B), IC2.7 (OUTB), J1.2 (TIP), J2.2 (TIP), J4.2 (TIP), J7.2 (TIP), J8.2 (TIP), J9.6, R1.2, R2.2, R3.1, R5.1, R7.1, R8.1, R9.1, R16.1, R18.1, R22.1, R29.1, R36.1
D0/RX: JP1.3, TX_LINK.2, U1_TQFP.30 (PD0(RXD))
D1/TX: JP1.2, RX_LINK1.2, U1_TQFP.31 (PD1(TXD))
D2: JP2.6, TP9.TP, U1_TQFP.32 (PD2(INT0)), U$14.IRQ
D3: TP8.TP, TX_LINK4.1, U1_TQFP.1 (PD3(INT1)), U$13.6
D4: S3.4, U1_TQFP.2 (PD4(XCK/T0))
D5: S3.3, U1_TQFP.9 (PD5(T1))
D6: TP2.TP, U1_TQFP.10 (PD6(AIN0))
D7: TP1.TP, TX_LINK6.1, U1_TQFP.11 (PD7(AIN1))
D8: R33.2, TP6.TP, TX_LINK1.1, TX_LINK2.1, TX_LINK3.1, U1_TQFP.12 (PB0(ICP)), U$13.4
D9: R10.2, U1_TQFP.13 (PB1(OC1A))
D10: JP2.2, R24.1, U1_TQFP.14 (PB2(SS/OC1B)), U$14.SEL
D11/MOSI: ISP1.4, JP2.5, U1_TQFP.15 (PB3(MOSI/OC2)), U$14.SDI
D12/MISO: ISP1.1, JP2.4, U1_TQFP.16 (PB4(MISO)), U$14.SDO
D13/SCK: ISP1.3, JP2.3, U1_TQFP.17 (PB5(SCK)), U$14.SCK
D+: D7.K (C), IC3.4 (D+), USB-C.A6 (D1+)
D-: D8.K (C), IC3.5 (D-), USB-C.A7 (D1-)
DIG1: C20.1, J$1.SIG (SIGNAL), U$14.ANT
DS18B20: JP2.1
DTR: C23.1, IC3.28 (DTR), JP1.1
GND: C1.2, C3.2, C4.2, C5.1, C6.1, C7.1, C10.2, C11.2, C16.2, C18.2, C20.2, C22.2, D7.A, D8.A, IC3.3 (GND), IC3.EXP (GND), IC3.M (GND), ISP1.6, J9.3, J12.1, J13.1, J14.1, J$1.GND@0 (GND), J$1.GND@1 (GND), J$1.GND@2 (GND), J$1.GND@3 (GND), JP1.6, LED1.C, S3.1, S3.2, TP3.TP, U1_TQFP.3 (GND), U1_TQFP.5 (GND), U$6.1 (GND), U$13.5, U$14.GND, U$14.P$12 (GND), USB-C.A1/B12 (GND1), USB-C.B1/A12 (GND2), USB-C.GND1 (SHIELD), USB-C.GND2 (SHIELD), USB-C.GND3 (SHIELD), USB-C.GND4 (SHIELD)
unnamed: C4.1, Q1.2, U1_TQFP.7 (PB6(XTAL1/TOSC1))
unnamed: J4.1 (SLEEVE), R9.2, R22.2, R25.2
unnamed: C18.1, IC3.6 (VDD)
unnamed: IC3.26 (TXD), TX_LINK.1
unnamed: IC3.25 (RXD), RX_LINK1.1
unnamed: J9.5, R1.1, R2.1, R28.2
unnamed: J7.1 (SLEEVE), R16.2, R18.2, R26.1
unnamed: C11.1, Q1.1, U1_TQFP.8 (PB7(XTAL2/TOSC2))
unnamed: J1.1 (SLEEVE), R5.2, R7.2, R19.1
unnamed: J8.1 (SLEEVE), R29.2, R36.2, R37.1
unnamed: J2.1 (SLEEVE), R3.2, R8.2, R20.1
unnamed: J12.2, TX_LINK1.2, TX_LINK6.2
unnamed: J13.2, TX_LINK2.2, TX_LINK5.2
unnamed: C17.2, IC2.5 (+IN_B), RBB.2, RBT.1
unnamed: J14.2, TX_LINK3.2, TX_LINK4.2
unnamed: IC1.7 (OUT), IC1.8 (FEEDBACK), R34.2, R35.2
unnamed: LED1.A, R10.1
RESET: C23.2, ISP1.5, R32.1, U1_TQFP.29 (PC6(/RESET))

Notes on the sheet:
AC-AC 9V measurement
OpenEnergyMonitor.org
Trystan Lea & Glyn Hudson - March 2022
for battery 6V max
Power
ATmega328
CT Current Sensors
Temperature & AC Voltage Sensors
Design is provided "AS IS" and "WITH ALL FAULTS. OpenEnergyMonitor DISCLAIMS ALL OTHER WARRANTIES, EXPRESS OR IMPLIED,
Hardware design files are licensed under the Creative Commons Attribution-ShareAlike 3.0 Unported License
emonTx V3.4.2
D19 / ADC 5 DS18B20 PWR
D5 - one-wire data
D3 - IRQ1 PQM
ATMEGA328
RFM12B RFM1269CW
One-Wire RJ45
D3 - IRQ1 PWM
D8 - one-wire data
ADC6 / Dig20
DIP Switch

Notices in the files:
firmware/EmonTxV4_6x_temperature/EmonTxV4_6x_temperature.ino:
Licence: GNU GPL V3
parts and their libraries:
SparkFun-DigitalIC: Licensing: CC v3.0 Share-Alike You are welcome to use this library for commercial purposes.
microbuilder: This work is placed in the public domain, and may be freely used for commercial and non-commercial work with the following conditions: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
